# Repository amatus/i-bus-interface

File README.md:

i-bus-interface
===============

This project consists of a Bluetooth adapter that is connected
to the BMW I-Bus and an Android app that talks to the I-Bus
using the adapter.

The main goal of this project is to use the up and down buttons on
the BMW E46 steering wheel to send previous track and next track
commands to the music player on an Android device.

Cadsoft Eagle v6 files for the adapter are in the hardware directory
and Android software is in the android directory.

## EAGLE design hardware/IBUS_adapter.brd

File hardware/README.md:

IBUS_adapter board
==================

The IBUS_adapter board is designed to adapt the I-Bus signals to
TTL serial at 9600 baud 8E1. The serial pinout is compatible with
the Virtuabotix [BT2S] Bluetooth Serial Slave device.

I stuffed this board, the BT2S, and the board from a cheap USB phone
car charger into a small project box and connected it to the 3-pin
plug formerly connected to the Sirius satellite radio module in the
trunk of my BMW.

In future revisions I may integrate the 5 V power supply into this board.

Configuring the BT2S
--------------------

The bluetooth module on the BT2S seems to be a Guangzhou HC
Information Technology Co. [HC-06]. The full command set can be
found in the linked PDF. The module defaults to 9600 8N1 and in order
to change this to 8E1 AT-commands need to be sent to it over the serial
interface. I used an FT232R breakout board and minicom to communicate
with the module. The commands are sent without any pauses between bytes
and are terminated with a pause. They are *not* terminated with a carriage
return or line feed. The easiest way to achieve this is to type the command
out and copy it to the clipboard without a terminating newline, then paste
it into your terminal program. The commands are also not echoed, only the
response will appear in the terminal. The command for changing the parity
to even is `AT+PE`. This does not change the parity for the command
interface, only bluetooth passthrough, so the terminal parity should be left
at none.

Other useful commands:
* `AT+NAMExxxx` will change the name of the device for bluethooth
  discovery to xxxx.
* `AT+PIN0000` will change the pairing code to 0000 (must be 4 digits).

  [bt2s]: https://www.virtuabotix.com/?page_id=3117&productid=609224531705
  [hc-06]: http://www.mcu-turkey.com/wp-content/uploads/2013/01/HC-Serial-Bluetooth-Products-201104.pdf

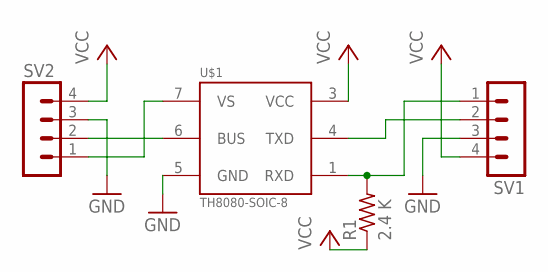
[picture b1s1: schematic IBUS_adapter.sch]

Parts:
R1: 2.4 K; R1206
SV1, SV2: MA04-1
U$1: TH8080-SOIC-8; SO-8

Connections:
GND: SV1.3, SV2.3, U$1.5 (GND)
unnamed: R1.2, SV1.1, U$1.1 (RXD)
unnamed: SV1.2, U$1.4 (TXD)
unnamed: SV2.2, U$1.6 (BUS)
unnamed: SV2.1, U$1.7 (VS)
VCC: R1.1, SV1.4, SV2.4, U$1.3 (VCC)

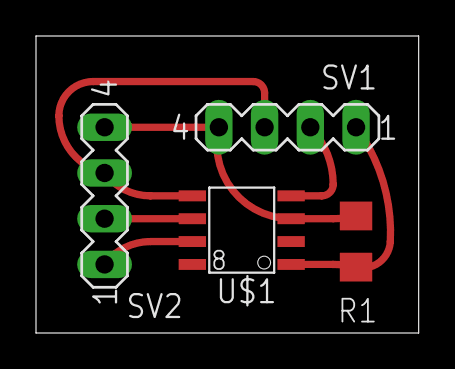
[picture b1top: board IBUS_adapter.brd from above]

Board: 2 copper layers, 21.3 x 16.5 mm, 4 parts (0 on the bottom side), 6 nets.

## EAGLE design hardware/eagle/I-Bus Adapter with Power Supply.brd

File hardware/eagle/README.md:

I-Bus Adapter board
==================

The I-Bus Adapter board is designed to adapt the I-Bus signals to
TTL serial at 9600 baud 8E1. The serial pinout is compatible with
the Virtuabotix [BT2S] Bluetooth Serial Slave device.

I stuffed this board, the BT2S, and the board from a cheap USB phone
car charger into a small project box and connected it to the 3-pin
plug formerly connected to the Sirius satellite radio module in the
trunk of my BMW.

I-Bus Adapter with Power Supply
===============================

This is the same ciruit with the addition of a power supply based on
the MC34063 switching regulator.

Configuring the BT2S
====================

The bluetooth module on the BT2S seems to be a Guangzhou HC
Information Technology Co. [HC-06]. The full command set can be
found in the linked PDF. The module defaults to 9600 8N1 and in order
to change this to 8E1 AT-commands need to be sent to it over the serial
interface. I used an FT232R breakout board and minicom to communicate
with the module. The commands are sent without any pauses between bytes
and are terminated with a pause. They are *not* terminated with a carriage
return or line feed. The easiest way to achieve this is to type the command
out and copy it to the clipboard without a terminating newline, then paste
it into your terminal program. The commands are also not echoed, only the
response will appear in the terminal. The command for changing the parity
to even is `AT+PE`. This does not change the parity for the command
interface, only bluetooth passthrough, so the terminal parity should be left
at none.

Other useful commands:
* `AT+NAMExxxx` will change the name of the device for bluethooth
  discovery to xxxx.
* `AT+PIN0000` will change the pairing code to 0000 (must be 4 digits).
* `AT+PN` will set the parity back to none.

  [bt2s]: https://www.virtuabotix.com/?page_id=3117&productid=609224531705
  [hc-06]: http://www.mcu-turkey.com/wp-content/uploads/2013/01/HC-Serial-Bluetooth-Products-201104.pdf

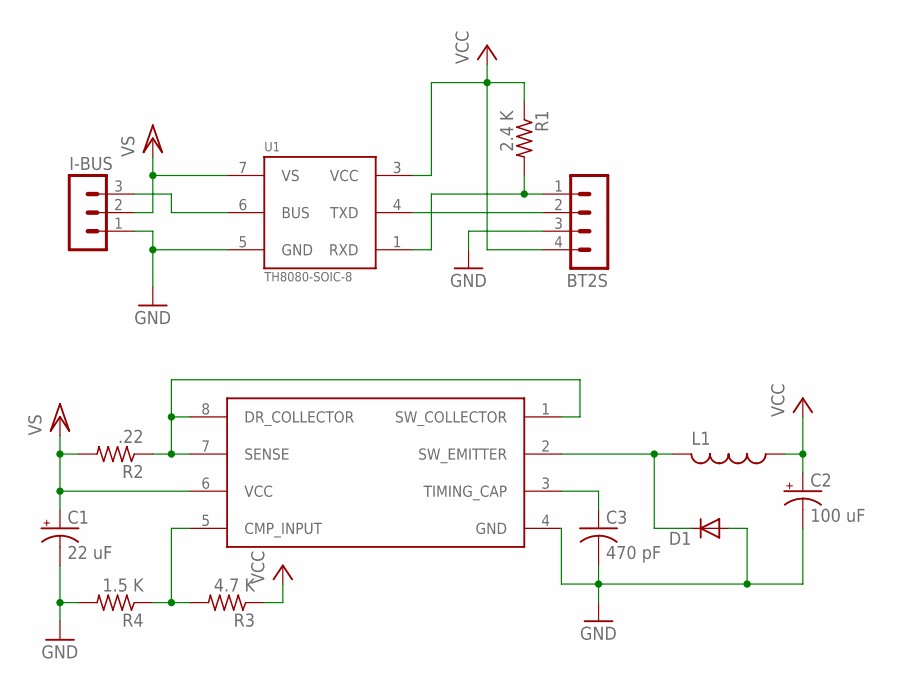
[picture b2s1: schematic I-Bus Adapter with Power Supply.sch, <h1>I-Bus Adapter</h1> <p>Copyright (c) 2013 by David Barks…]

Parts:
BT2S: MA04-1
C1: 22 uF; E1,8-4
C2: 100 uF; E1,8-4
C3: 470 pF; C0603K
D1: DIODE-D-2.5; D-2.5
I-BUS: MA03-1
L1: L-US0207/2V; 0207/2V
R1: 2.4 K; R1206
R2: .22; R1206
R3: 4.7 K; R2012
R4: 1.5 K; R2012
U1: TH8080-SOIC-8; SO-8
U2: MC34063-SOIC-8; SO-8

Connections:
GND: BT2S.3, C1.-, C2.-, C3.2, D1.A, I-BUS.1, R4.2, U1.5 (GND), U2.4 (GND)
unnamed: BT2S.1, R1.2, U1.1 (RXD)
unnamed: BT2S.2, U1.4 (TXD)
unnamed: R2.1, U2.1 (SW_COLLECTOR), U2.7 (SENSE), U2.8 (DR_COLLECTOR)
unnamed: I-BUS.3, U1.6 (BUS)
unnamed: D1.C, L1.2, U2.2 (SW_EMITTER)
unnamed: R3.2, R4.1, U2.5 (CMP_INPUT)
unnamed: C3.1, U2.3 (TIMING_CAP)
VCC: BT2S.4, C2.+, L1.1, R1.1, R3.1, U1.3 (VCC)
VCC/2: C1.+, I-BUS.2, R2.2, U1.7 (VS), U2.6 (VCC)

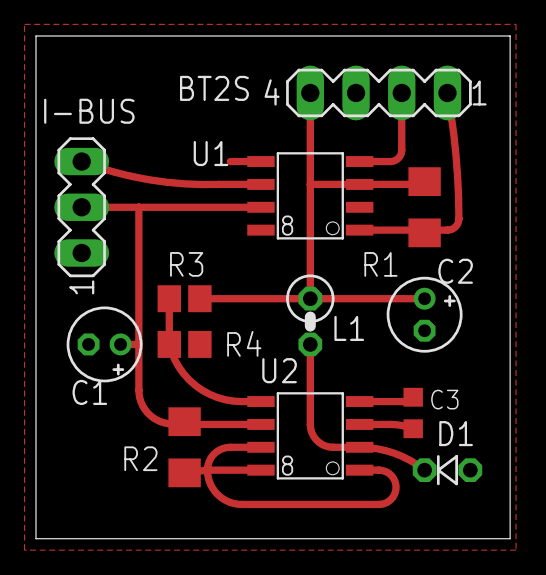
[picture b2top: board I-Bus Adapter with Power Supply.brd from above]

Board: 2 copper layers, 26.3 x 27.9 mm, 13 parts (0 on the bottom side), 10 nets.

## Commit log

2013-05-12 I-Bus adapter board design.
2013-05-12 Added comments on configuring the BT2S.
2013-05-12 Better wording.
2013-05-13 Added CC BY-SA 3.0 license to hardware designs.
2013-05-14 New design with power supply.
    I added a power supply and updated the readme.
2013-05-16 Created new IBusIntents android project.
2013-05-17 We'll use a service to monitor I-Bus messages.
2013-05-17 Added .gitingore
2013-05-17 Updated main readme.
2013-05-18 Connect to BT2S and read from it.
2013-05-21 Use checksum for message synchronization.
    We've lost the framing information over bluetooth, one way to
    try to recover synchronization is to check message checksum.
2013-05-23 Added steering wheel button events.
2013-05-25 Fix previous command.
2014-02-17 New design based on the TI CC2541
2014-02-17 Rules check found missing NCs
2014-02-20 New version using the MCP2025
2014-02-20 Initial module assignments
2014-02-21 Component placement, fixed some modules
2014-02-22 Changed power supply caps.
2014-02-22 Added .gitignore
2014-02-22 New module for C1
2014-02-23 Changed the LEDs to active-low
2014-02-23 Some work on layout, upgraded kicad
2014-02-23 Initial layout finished
2014-02-23 Embiggened power and RF traces
2014-02-23 Connect thermal pad to ground
2014-02-23 RF review and reconnected debug pins
2014-02-23 RF review, better placement
2014-02-23 Placed references and values
2014-02-23 Fixed LEDs
2014-02-23 Fix connectivity
2014-02-23 Generated gerbers, not sure what changed
2014-02-23 Tweaking fill clearance
    Why do fills not avoid masked areas?
2014-02-23 Labeled headers
2014-03-30 Fix C1 silkscreen.

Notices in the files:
hardware/I-Bus Adapter with Power Supply.sch:
Copyright (c) 2013 by David Barksdale. This work is made available under the terms of the Creative Commons Attribution-ShareAlike 3.0 license, http://creativecommons.org/licenses/by-sa/3.0/.
